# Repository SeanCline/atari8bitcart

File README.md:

# Cartridge for 8-Bit Atari Computers (400/800/XL/XE)

Configurable Atari 8-bit cartridge PCB for the Atari 400/800/XL/XE line of home computers.

1. **Single 8 KB mode** using one 2764-compatible PROM in the right-hand socket.
2. **Dual 8 KB + 8 KB mode** using two 2764-compatible PROMs.
3. **Single 16 KB mode** using one 27128-compatible PROM in the right-hand socket along with a `74AHCT1G08` for chip-enable logic.

## Hardware Summary

- **U0**: accepts either:
  - a 2764-compatible (8 KB) PROM for both 8KB and 8KB+8KB configurations.
  - a 27128-compatible (16 KB) PROM for 16 KB configurations.
- **U1**: accepts a 2764-compatible (8 KB) PROM in the 8KB+8KB configuration.
- **U2**: `74AHCT1G08` single AND gate used to merge the two chip-enable lines (/S4 and /S5) into a single signal for the 16KB configuration.
- **C0 / C1**: 100 nF bypass capacitors.

## Jumper Configuration

The jumpers are organized into sections, one for each supported configuration.

> ℹ️ **Bridge only the jumpers required for the configuration you intend to use.**

## Releases

The latest gerber files can be found in the build artifacts section of the [Actions](https://github.com/SeanCline/atari8bitcart/actions) tab.
At the moment, the gerbers are generated for JLCPCB, but it should be pretty easy to send them to a PCB fab of your choosing.

## Schematic

## License

CERN-OHL-W-2.0

See [LICENSE.txt](LICENSE.txt).

---

**Trademark notice:** Atari is a trademark of its respective owner. This project is an independent, unofficial hardware design and is not affiliated with or endorsed by Atari.

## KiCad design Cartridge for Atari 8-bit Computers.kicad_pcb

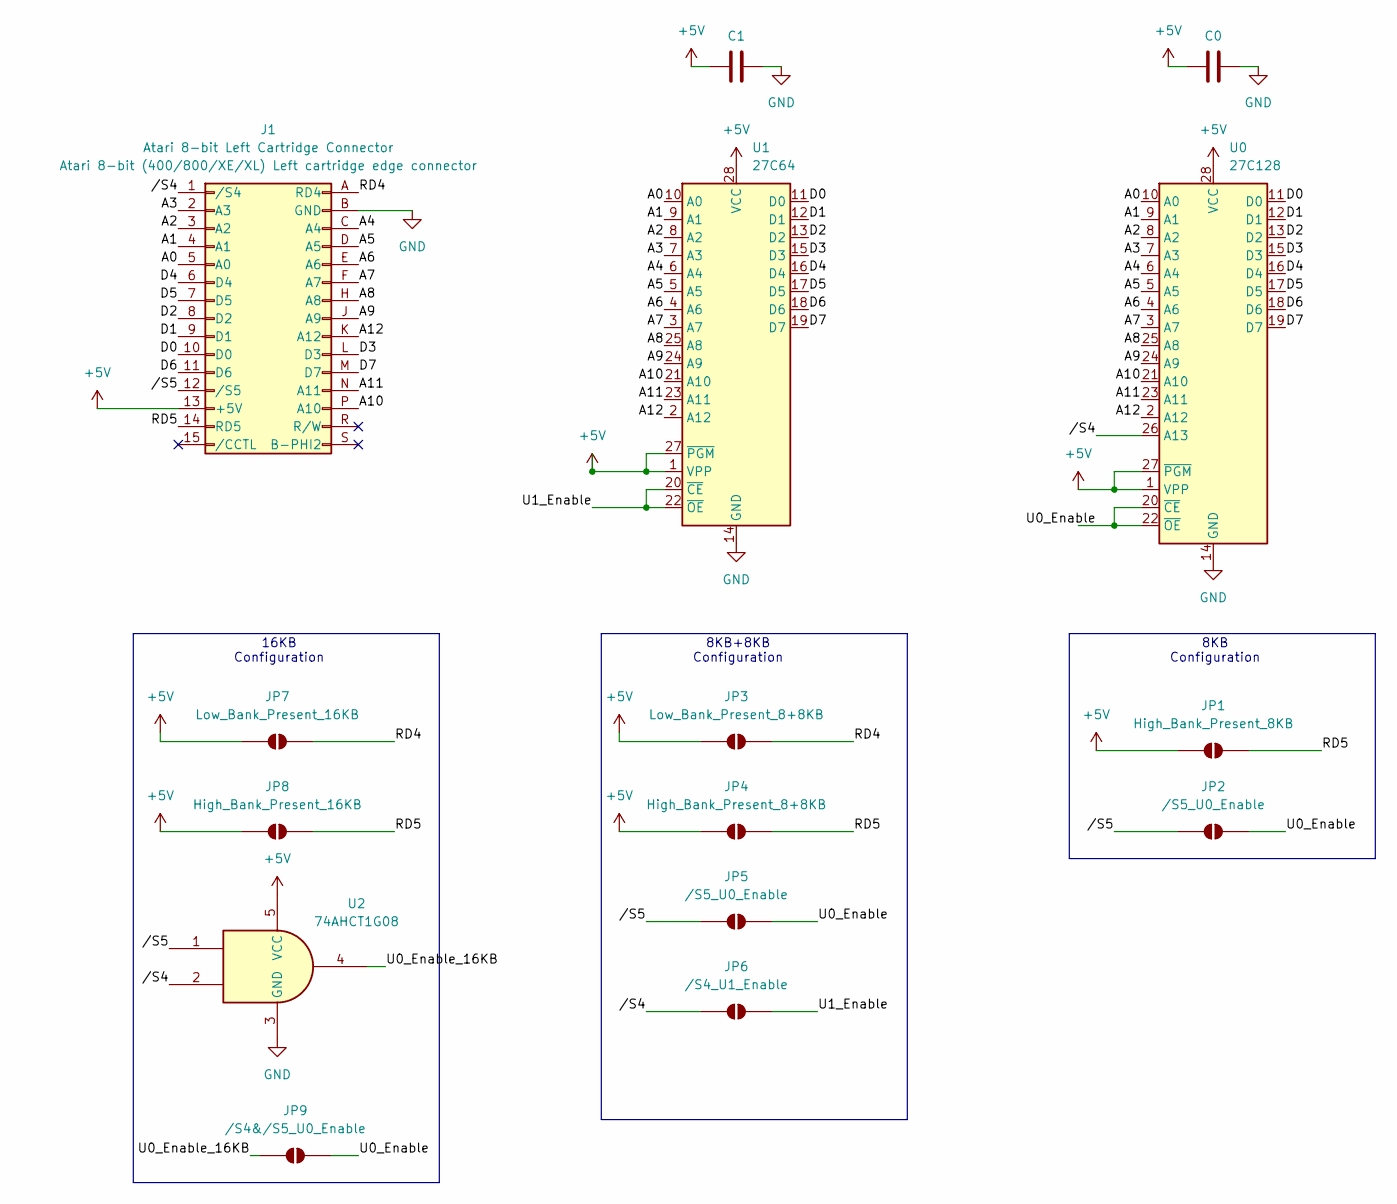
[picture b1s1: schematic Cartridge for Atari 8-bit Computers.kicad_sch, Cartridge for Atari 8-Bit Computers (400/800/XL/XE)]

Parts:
C0, C1: 100nF; C_Disc_D5.0mm_W2.5mm_P5.00mm; LCSC C2896060
J1: Atari 8-bit Left Cartridge Connector; Atari_8-bit_Cartridge_Connector
JP1: High_Bank_Present_8KB; SolderJumper
JP2, JP5: /S5_U0_Enable; SolderJumper
JP3: Low_Bank_Present_8+8KB; SolderJumper
JP4: High_Bank_Present_8+8KB; SolderJumper
JP6: /S4_U1_Enable; SolderJumper
JP7: Low_Bank_Present_16KB; SolderJumper
JP8: High_Bank_Present_16KB; SolderJumper
JP9: /S4&/S5_U0_Enable; SolderJumper
U0: 27C128; DIP-28_W15.24mm; LCSC C72121
U1: 27C64; DIP-28_W15.24mm; LCSC C72121
U2: 74AHCT1G08; SOT-353_SC-70-5; LCSC C460499

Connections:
+5V: C0.1, C1.1, J1.13 (+5V), JP1.1 (A), JP3.1 (A), JP4.1 (A), JP7.1 (A), JP8.1 (A), U0.1 (VPP), U0.27 (~PGM), U0.28 (VCC), U1.1 (VPP), U1.27 (~PGM), U1.28 (VCC), U2.5 (VCC)
/A0: J1.5 (A0), U0.10 (A0), U1.10 (A0)
/A1: J1.4 (A1), U0.9 (A1), U1.9 (A1)
/A2: J1.3 (A2), U0.8 (A2), U1.8 (A2)
/A3: J1.2 (A3), U0.7 (A3), U1.7 (A3)
/A4: J1.C (A4), U0.6 (A4), U1.6 (A4)
/A5: J1.D (A5), U0.5 (A5), U1.5 (A5)
/A6: J1.E (A6), U0.4 (A6), U1.4 (A6)
/A7: J1.F (A7), U0.3 (A7), U1.3 (A7)
/A8: J1.H (A8), U0.25 (A8), U1.25 (A8)
/A9: J1.J (A9), U0.24 (A9), U1.24 (A9)
/A10: J1.P (A10), U0.21 (A10), U1.21 (A10)
/A11: J1.N (A11), U0.23 (A11), U1.23 (A11)
/A12: J1.K (A12), U0.2 (A12), U1.2 (A12)
/D0: J1.10 (D0), U0.11 (D0), U1.11 (D0)
/D1: J1.9 (D1), U0.12 (D1), U1.12 (D1)
/D2: J1.8 (D2), U0.13 (D2), U1.13 (D2)
/D3: J1.L (D3), U0.15 (D3), U1.15 (D3)
/D4: J1.6 (D4), U0.16 (D4), U1.16 (D4)
/D5: J1.7 (D5), U0.17 (D5), U1.17 (D5)
/D6: J1.11 (D6), U0.18 (D6), U1.18 (D6)
/D7: J1.M (D7), U0.19 (D7), U1.19 (D7)
/RD4: J1.A (RD4), JP3.2 (B), JP7.2 (B)
/RD5: J1.14 (RD5), JP1.2 (B), JP4.2 (B), JP8.2 (B)
/U0_Enable: JP2.2 (B), JP5.2 (B), JP9.1 (A), U0.20 (~CE), U0.22 (~OE)
/U0_Enable_16KB: JP9.2 (B), U2.4
/U1_Enable: JP6.2 (B), U1.20 (~CE), U1.22 (~OE)
//S4: J1.1 (/S4), JP6.1 (A), U0.26 (A13), U2.2
//S5: J1.12 (/S5), JP2.1 (A), JP5.1 (A), U2.1
GND: C0.2, C1.2, J1.B (GND), U0.14 (GND), U1.14 (GND), U2.3 (GND)

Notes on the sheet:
16KB Configuration
8KB Configuration
8KB+8KB Configuration

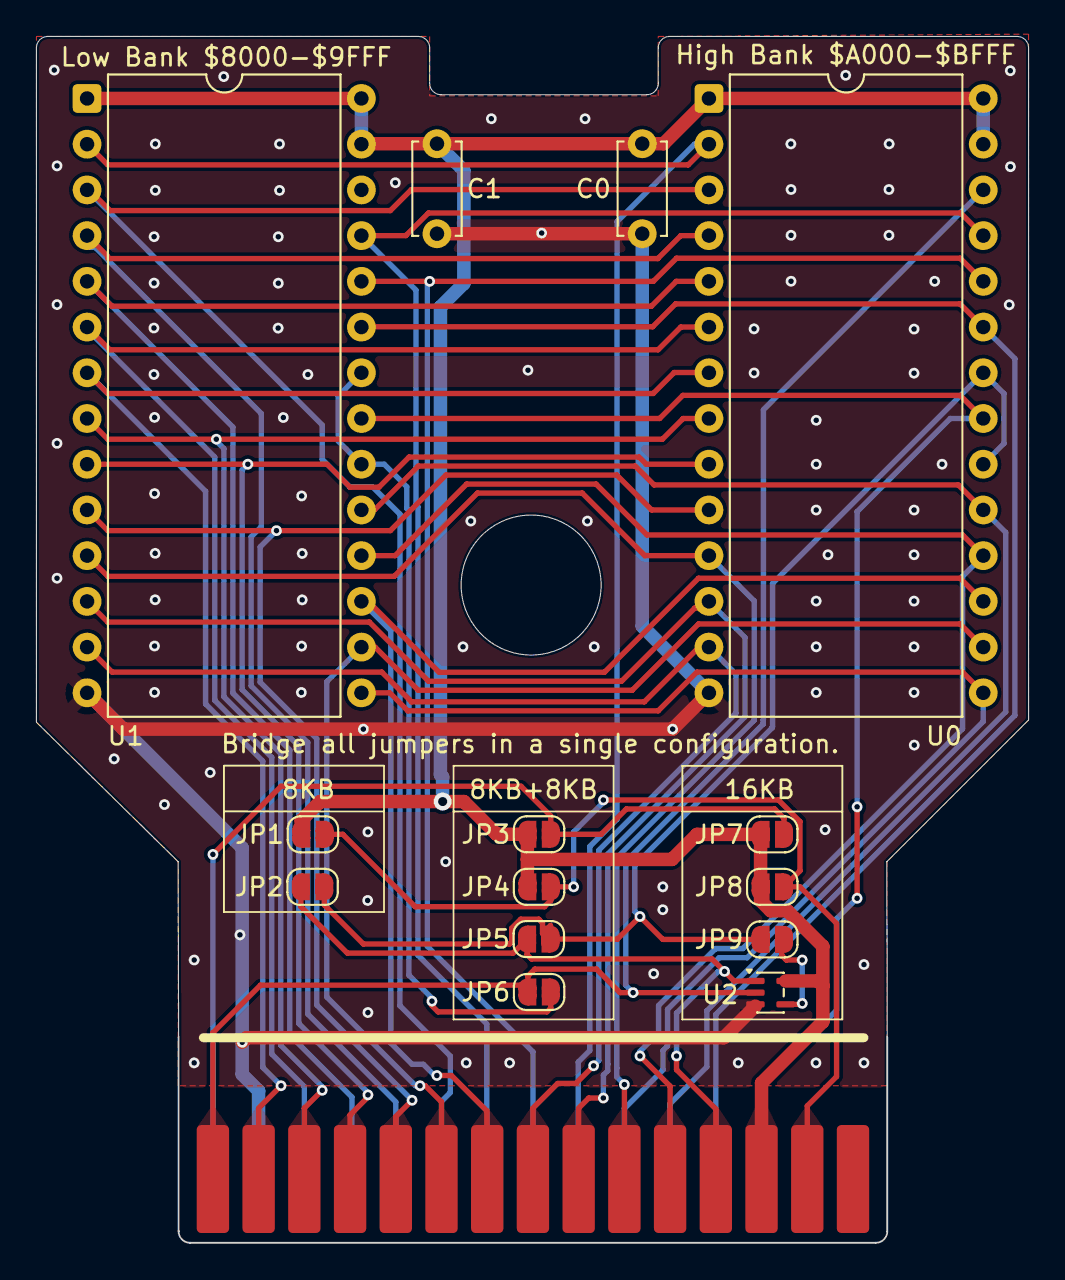
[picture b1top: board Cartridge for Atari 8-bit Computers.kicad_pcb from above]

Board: 2 copper layers, 55.1 x 67.0 mm, 15 parts (0 on the bottom side), 30 nets.

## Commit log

2026-04-17 Initial Commit. Schematic mostly decoded.
2026-04-18 Create footprint for cart edge connector.
2026-04-19 Add PCB edge cuts and rough layout.
2026-04-19 Preliminary board layout.
2026-04-19 Increase hole and notch size for better fit with case.
2026-04-21 Lay out configuration jumpers.
    This required moving quite a bit around to make room.
2026-04-21 Add some conservative DRC constraints.
    Consulted JLCPCB's capabilities, and added some wiggle room.
2026-04-21 Finish routing front and back copper.
2026-04-21 Remove soldermask from edge connector.
    It can wear off and gunk up the cartridge slot.
2026-04-21 First routing pass of back copper.
2026-04-21 Add README.md and LICENSE.txt
2026-04-21 Add ground fills and via stitching.
2026-04-22 Rename the project.
    `Atari` being at the beginning of the name makes it seem like it's an
    official project. Renaming should prevent any confusion.
2026-04-22 Build the JLCPCB gerbers as a Github action.
    Additionally, fix some DRC errors introduced with the stitching vias and
    add a copyright disclaimer to the readme.
2026-04-22 Add LCSC component part numbers for assembly.
2026-04-22 Remove JLCJLCJLCJLC placeholder text for run number.
    It seems JLCPCB no longer needs a production run number anymore.
    Additionally, generate preview images as during the CI build.
2026-04-22 Change the CI's docker image to Kicad 10 instead of the nightly builds.
2026-04-22 Change the PCB color to black.
2026-04-23 Add images to README.md
2026-04-23 Allow through-hole components when generating the BOM/CPL.
2026-04-23 Update Github action to fix deprecation warnings.
2026-04-23 Exclude solder jumper footprints from the CPL file.
    Fabs can get confused when a component exists in the CPL but not in the
    BOM.
2026-05-05 Add an image of each configuration.
    Not pretty, but it gets the point across.
2026-05-28 Minor correction to jump configuration diagram.
